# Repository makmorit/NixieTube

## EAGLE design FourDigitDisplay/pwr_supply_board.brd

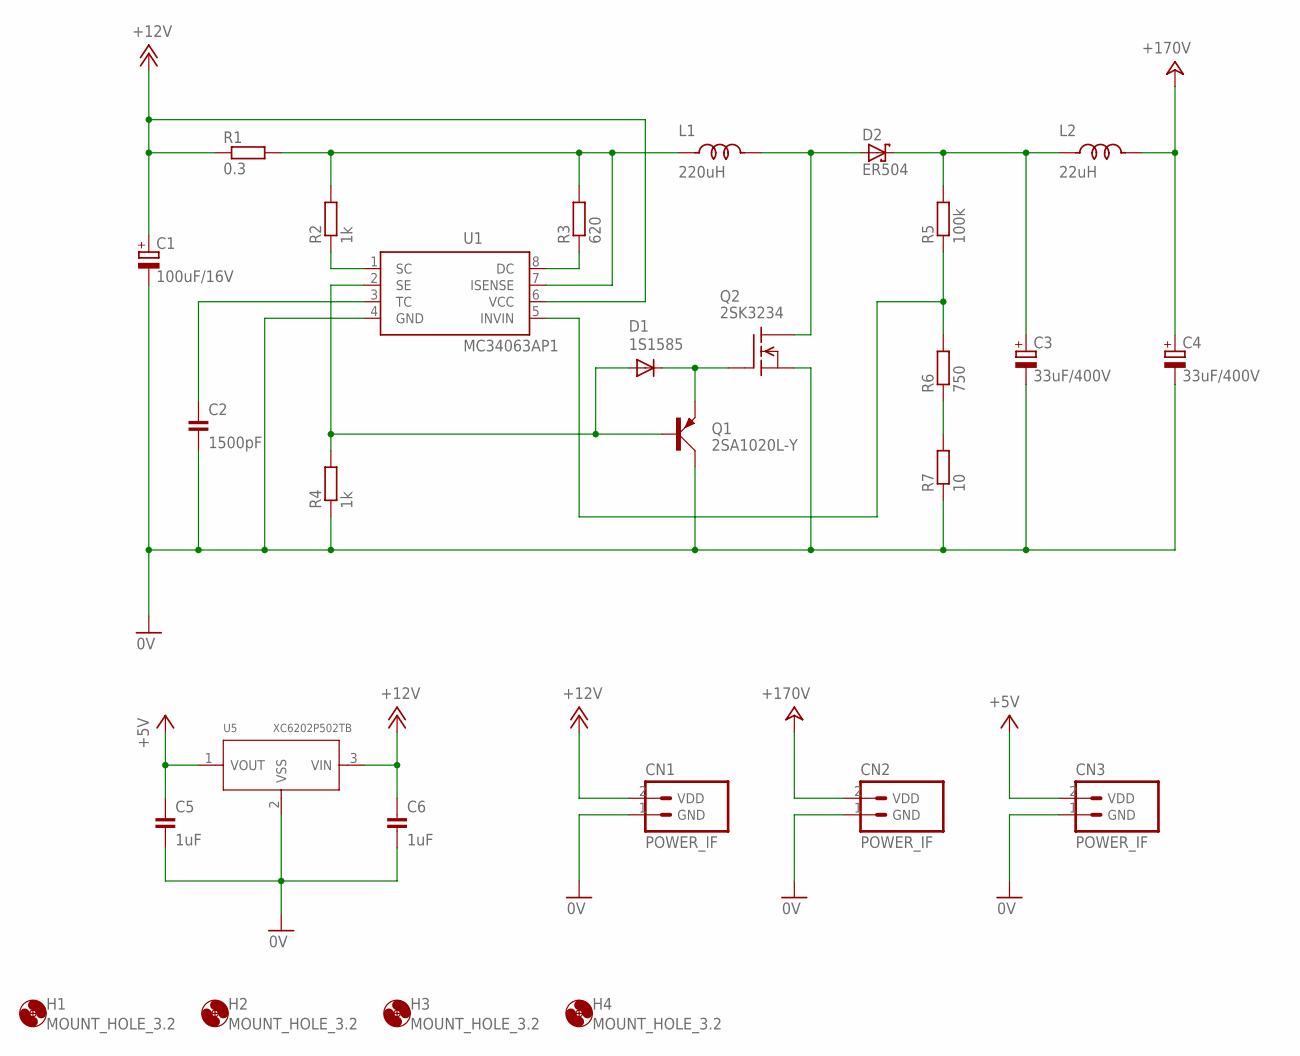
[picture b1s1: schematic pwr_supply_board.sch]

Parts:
C1: 100uF/16V; ELECAP_100MIL
C2: 1500pF; CAP_100MIL
C3, C4: 33uF/400V; ELECAP_300MIL
C5, C6: 1uF; CAP_100MIL
CN1, CN2, CN3: POWER_IF; HEADER_2PIN_POWER_IF
D1: 1S1585; DIODE-200MIL
D2: ER504; DIODE-500MIL
H1, H2, H3, H4: MOUNT_HOLE_3.2; 3,2
L1: 220uH; TOROID_COIL-300MIL
L2: 22uH; TOROID_COIL-300MIL
Q1: 2SA1020L-Y; TO-92NL
Q2: 2SK3234; TO-220
R1: 0.3; RESISTOR_0411_600MIL
R2, R4: 1k; RESISTOR_0411_600MIL
R3: 620; RESISTOR_0411_600MIL
R5: 100k; RESISTOR_0411_600MIL
R6: 750; RESISTOR_0411_600MIL
R7: 10; RESISTOR_0411_600MIL
U1: MC34063AP1; DIL08
U5: XC6202P502TB; TO92-LINE

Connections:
0V: C1.-, C2.2, C3.-, C4.-, C5.2, C6.2, CN1.1 (GND), CN2.1 (GND), CN3.1 (GND), Q1.2 (C), Q2.3 (S), R4.1, R7.1, U1.4 (GND), U5.2 (VSS)
+5V: C5.1, CN3.2 (VDD), U5.1 (VOUT)
+12V: C1.+, C6.1, CN1.2 (VDD), R1.1, U1.6 (VCC), U5.3 (VIN)
+24V: C4.+, CN2.2 (VDD), L2.2
unnamed: R3.1, U1.8 (DC)
unnamed: C3.+, D2.C, L2.1, R5.2
unnamed: C2.1, U1.3 (TC)
unnamed: R2.1, U1.1 (SC)
unnamed: L1.1, R1.2, R2.2, R3.2, U1.7 (ISENSE)
unnamed: R5.1, R6.2, U1.5 (INVIN)
unnamed: D1.A, Q1.3 (B), R4.2, U1.2 (SE)
unnamed: D1.C, Q1.1 (E), Q2.1 (G)
unnamed: R6.1, R7.2
unnamed: D2.A, L1.2, Q2.2 (D)

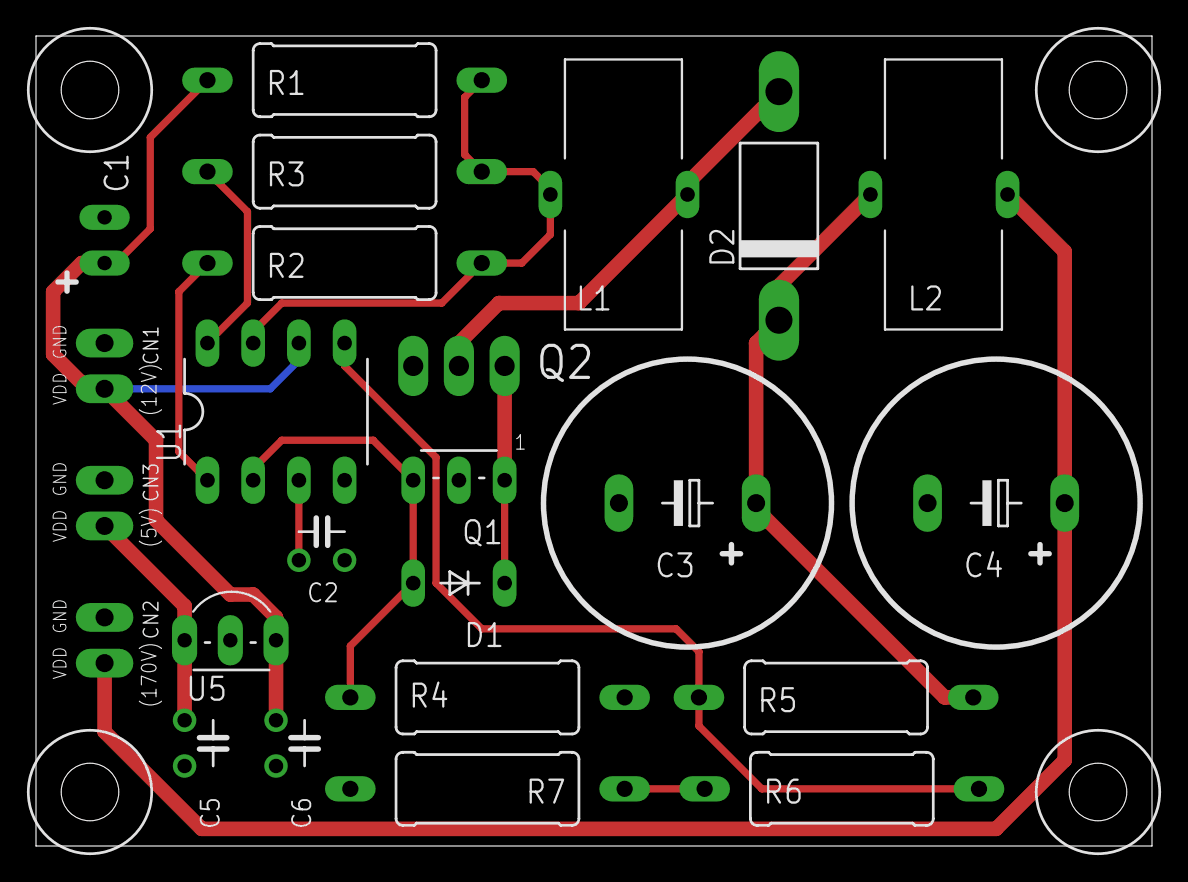
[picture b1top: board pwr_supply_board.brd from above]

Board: 2 copper layers, 62.0 x 45.0 mm, 28 parts (0 on the bottom side), 14 nets.

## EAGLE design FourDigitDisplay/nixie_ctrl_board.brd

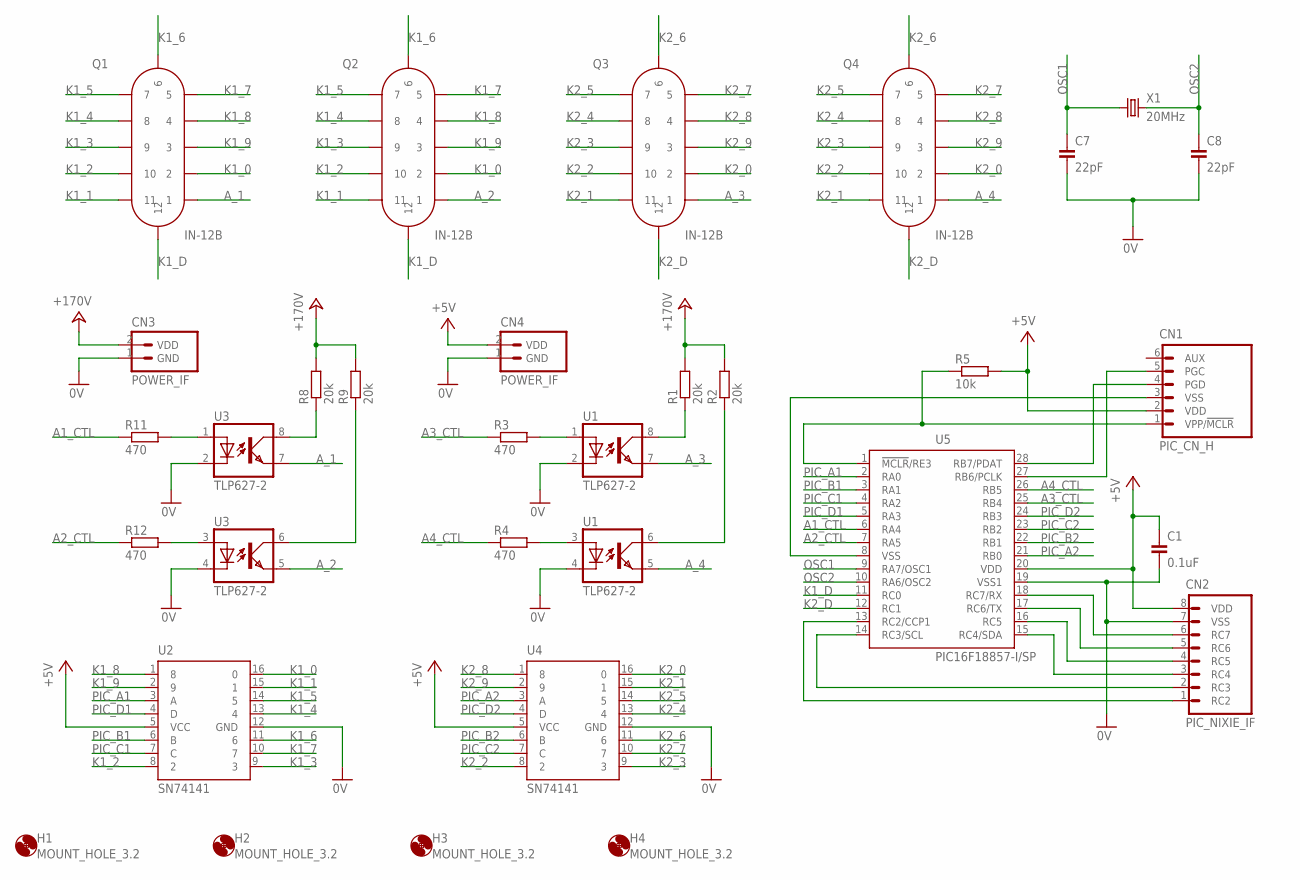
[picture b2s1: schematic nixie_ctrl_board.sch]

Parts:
C1: 0.1uF; CAP_100MIL
C7, C8: 22pF; CAP_100MIL
CN1: PIC_CN_H; HEADER_6PIN
CN2: PIC_NIXIE_IF; PIC_IF_NIXIE_8PIN
CN3, CN4: POWER_IF; HEADER_2PIN_POWER_IF
H1, H2, H3, H4: MOUNT_HOLE_3.2; 3,2
Q1, Q2, Q3, Q4: IN-12B; IN-12
R1, R2, R8, R9: 20k; RESISTOR_0207_300MIL
R3, R4, R11, R12: 470; RESISTOR_0204_200MIL
R5: 10k; RESISTOR_0204_200MIL
U1, U3: TLP627-2; DIL08
U2, U4: SN74141; DIL16
U5: PIC16F18857-I/SP; DIL28-3
X1: 20MHz; HC-49/S

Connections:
0V: C1.2, C7.2, C8.2, CN2.7 (VSS), CN3.1 (GND), CN4.1 (GND), U1.2 (C), U1.4 (C), U2.12 (GND), U3.2 (C), U3.4 (C), U4.12 (GND), U5.19 (VSS1)
+5V: C1.1, CN1.2 (VDD), CN2.8 (VDD), CN4.2 (VDD), R5.2, U2.5 (VCC), U4.5 (VCC), U5.20 (VDD)
+24V: CN3.2 (VDD), R1.2, R2.2, R8.2, R9.2
A1_CTL: R11.1, U5.6 (RA4)
A2_CTL: R12.1, U5.7 (RA5)
A3_CTL: R3.1, U5.25 (RB4)
A4_CTL: R4.1, U5.26 (RB5)
A_1: Q1.1, U3.7 (EMIT)
A_2: Q2.1, U3.5 (EMIT)
A_3: Q3.1, U1.7 (EMIT)
A_4: Q4.1, U1.5 (EMIT)
K1_0: Q1.2, Q2.2, U2.16 (0)
K1_1: Q1.11, Q2.11, U2.15 (1)
K1_2: Q1.10, Q2.10, U2.8 (2)
K1_3: Q1.9, Q2.9, U2.9 (3)
K1_4: Q1.8, Q2.8, U2.13 (4)
K1_5: Q1.7, Q2.7, U2.14 (5)
K1_6: Q1.6, Q2.6, U2.11 (6)
K1_7: Q1.5, Q2.5, U2.10 (7)
K1_8: Q1.4, Q2.4, U2.1 (8)
K1_9: Q1.3, Q2.3, U2.2 (9)
K1_D: Q1.12, Q2.12, U5.11 (RC0)
K2_0: Q3.2, Q4.2, U4.16 (0)
K2_1: Q3.11, Q4.11, U4.15 (1)
K2_2: Q3.10, Q4.10, U4.8 (2)
K2_3: Q3.9, Q4.9, U4.9 (3)
K2_4: Q3.8, Q4.8, U4.13 (4)
K2_5: Q3.7, Q4.7, U4.14 (5)
K2_6: Q3.6, Q4.6, U4.11 (6)
K2_7: Q3.5, Q4.5, U4.10 (7)
K2_8: Q3.4, Q4.4, U4.1 (8)
K2_9: Q3.3, Q4.3, U4.2 (9)
K2_D: Q3.12, Q4.12, U5.12 (RC1)
unnamed: R1.1, U1.8 (COL)
unnamed: R2.1, U1.6 (COL)
unnamed: R3.2, U1.1 (A)
unnamed: R4.2, U1.3 (A)
unnamed: CN2.6 (RC7), U5.18 (RC7/RX)
unnamed: CN2.5 (RC6), U5.17 (RC6/TX)
unnamed: CN1.1 (VPP/!MCLR), R5.1, U5.1 (!MCLR!/RE3)
unnamed: CN1.4 (PGD), U5.28 (RB7/PDAT)
unnamed: CN1.5 (PGC), U5.27 (RB6/PCLK)
unnamed: CN2.4 (RC5), U5.16 (RC5)
unnamed: R8.1, U3.8 (COL)
unnamed: R9.1, U3.6 (COL)
unnamed: R11.2, U3.1 (A)
unnamed: R12.2, U3.3 (A)
unnamed: CN1.3 (VSS), U5.8 (VSS)
unnamed: CN2.3 (RC4), U5.15 (RC4/SDA)
unnamed: CN2.2 (RC3), U5.14 (RC3/SCL)
unnamed: CN2.1 (RC2), U5.13 (RC2/CCP1)
OSC1: C7.1, U5.9 (RA7/OSC1), X1.1
OSC2: C8.1, U5.10 (RA6/OSC2), X1.2
PIC_A1: U2.3 (A), U5.2 (RA0)
PIC_A2: U4.3 (A), U5.21 (RB0)
PIC_B1: U2.6 (B), U5.3 (RA1)
PIC_B2: U4.6 (B), U5.22 (RB1)
PIC_C1: U2.7 (C), U5.4 (RA2)
PIC_C2: U4.7 (C), U5.23 (RB2)
PIC_D1: U2.4 (D), U5.5 (RA3)
PIC_D2: U4.4 (D), U5.24 (RB3)

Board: 2 copper layers, 30 parts (0 on the bottom side), 61 nets, no tracks yet.

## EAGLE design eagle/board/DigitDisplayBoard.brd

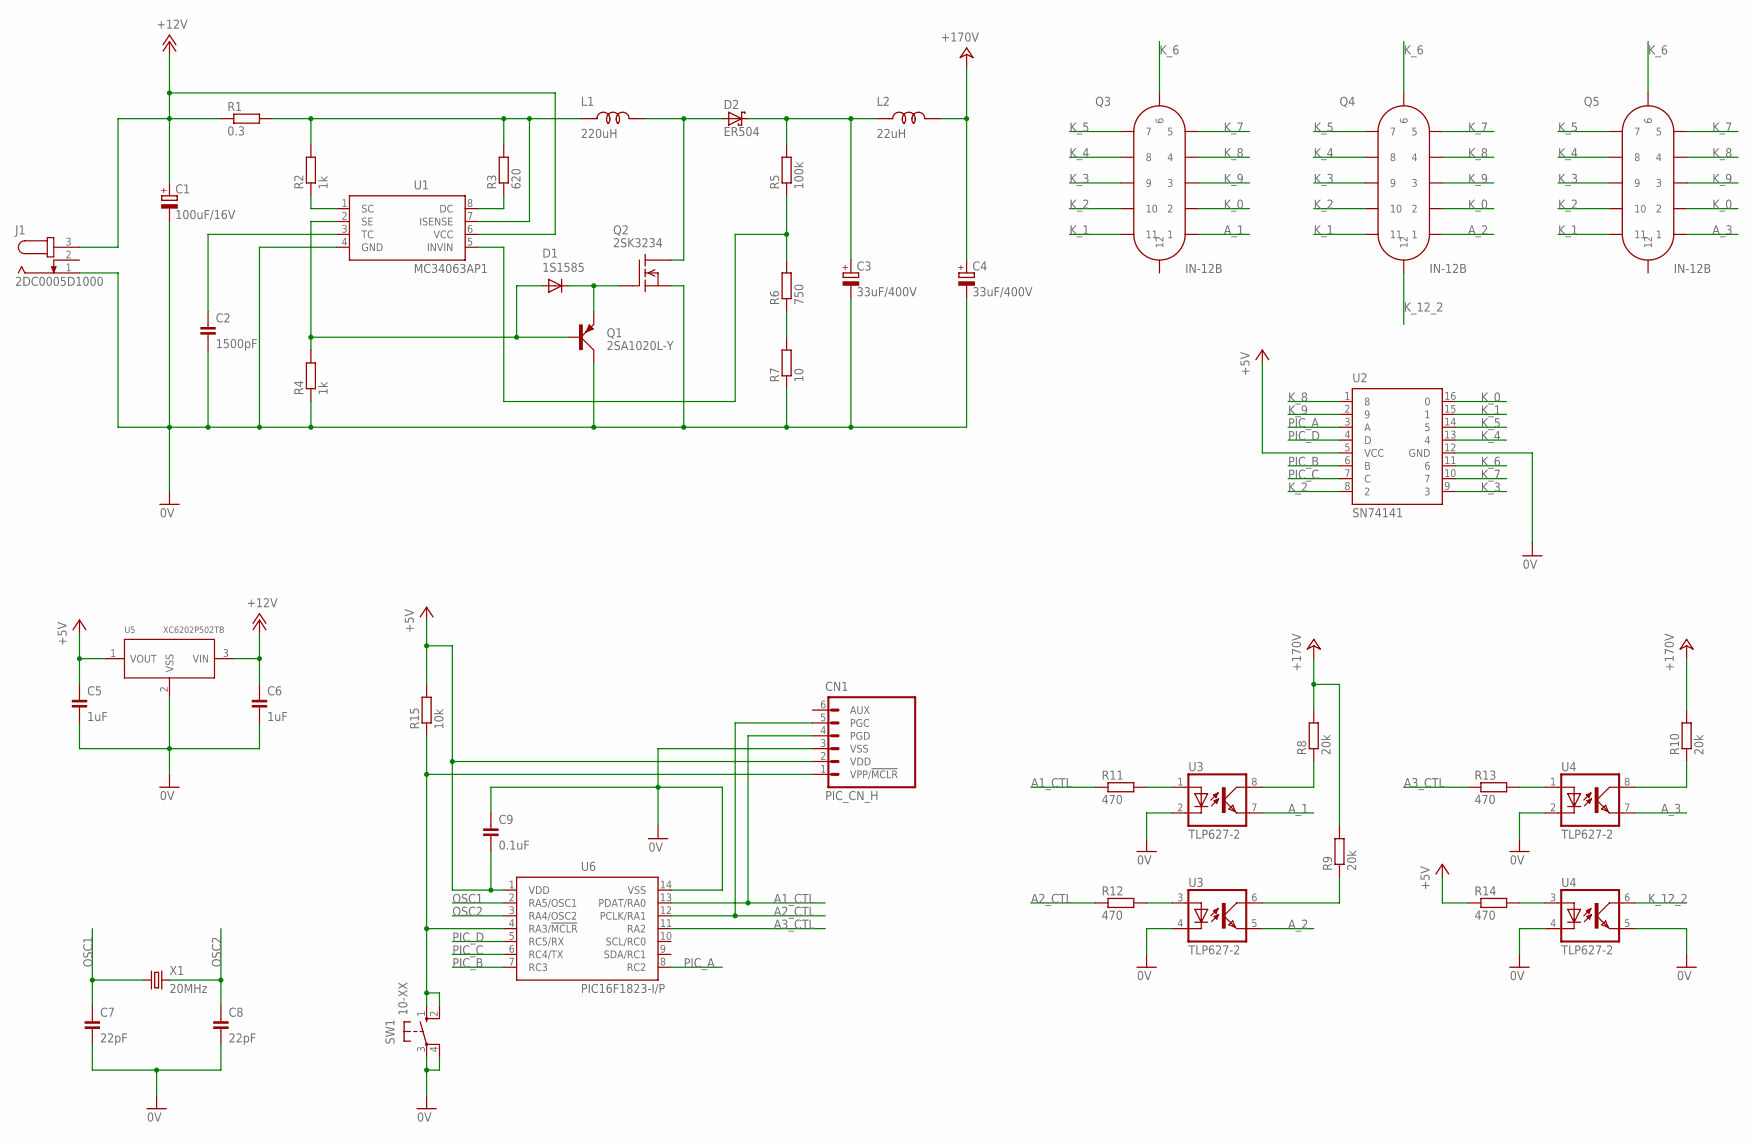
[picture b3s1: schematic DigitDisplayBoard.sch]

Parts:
C1: 100uF/16V; ELECAP_200MIL
C2: 1500pF; CAP_200MIL
C3, C4: 33uF/400V; ELECAP_300MIL
C5, C6: 1uF; CAP_200MIL
C7, C8: 22pF; CAP_200MIL
C9: 0.1uF; CAP_200MIL
CN1: PIC_CN_H; HEADER_6PIN
D1: 1S1585; DIODE-200MIL
D2: ER504; DIODE-500MIL
J1: 2DC0005D1000; DCJACK_2.1_5.5
L1: 220uH; TOROID_COIL-300MIL
L2: 22uH; TOROID_COIL-300MIL
Q1: 2SA1020L-Y; TO-92NL
Q2: 2SK3234; TO-220
Q3, Q4, Q5: IN-12B; IN-12
R1: 0.3; RESISTOR_0411_600MIL
R2, R4: 1k; RESISTOR_0411_600MIL
R3: 620; RESISTOR_0411_600MIL
R5: 100k; RESISTOR_0411_600MIL
R6: 750; RESISTOR_0411_600MIL
R7: 10; RESISTOR_0411_600MIL
R8, R10: 20k; RESISTOR_0207_300MIL
R9: 20k; RESISTOR_0411_600MIL
R11, R12, R13, R14: 470; RESISTOR_0207_300MIL
R15: 10k; RESISTOR_0207_300MIL
SW1: 10-XX; B3F-10XX
U1: MC34063AP1; DIL08
U2: SN74141; DIL16
U3, U4: TLP627-2; DIL08
U5: XC6202P502TB; TO92-LINE
U6: PIC16F1823-I/P; DIL14
X1: 20MHz; HC-49/S

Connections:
0V: C1.-, C2.2, C3.-, C4.-, C5.2, C6.2, C7.2, C8.2, C9.1, CN1.3 (VSS), J1.1, Q1.2 (C), Q2.3 (S), R4.1, R7.1, SW1.3, SW1.4 (P1), U1.4 (GND), U2.12 (GND), U3.2 (C), U3.4 (C), U4.2 (C), U4.4 (C), U4.5 (EMIT), U5.2 (VSS), U6.14 (VSS)
+5V: C5.1, C9.2, CN1.2 (VDD), R14.1, R15.2, U2.5 (VCC), U5.1 (VOUT), U6.1 (VDD)
+12V: C1.+, C6.1, J1.3, R1.1, U1.6 (VCC), U5.3 (VIN)
+24V: C4.+, L2.2, R8.2, R9.2, R10.2
A1_CTL: CN1.4 (PGD), R11.1, U6.13 (PDAT/RA0)
A2_CTL: CN1.5 (PGC), R12.1, U6.12 (PCLK/RA1)
A3_CTL: R13.1, U6.11 (RA2)
A_1: Q3.1, U3.7 (EMIT)
A_2: Q4.1, U3.5 (EMIT)
A_3: Q5.1, U4.7 (EMIT)
K_0: Q3.2, Q4.2, Q5.2, U2.16 (0)
K_1: Q3.11, Q4.11, Q5.11, U2.15 (1)
K_2: Q3.10, Q4.10, Q5.10, U2.8 (2)
K_3: Q3.9, Q4.9, Q5.9, U2.9 (3)
K_4: Q3.8, Q4.8, Q5.8, U2.13 (4)
K_5: Q3.7, Q4.7, Q5.7, U2.14 (5)
K_6: Q3.6, Q4.6, Q5.6, U2.11 (6)
K_7: Q3.5, Q4.5, Q5.5, U2.10 (7)
K_8: Q3.4, Q4.4, Q5.4, U2.1 (8)
K_9: Q3.3, Q4.3, Q5.3, U2.2 (9)
K_12_2: Q4.12, U4.6 (COL)
unnamed: R3.1, U1.8 (DC)
unnamed: C3.+, D2.C, L2.1, R5.2
unnamed: C2.1, U1.3 (TC)
unnamed: R2.1, U1.1 (SC)
unnamed: L1.1, R1.2, R2.2, R3.2, U1.7 (ISENSE)
unnamed: R5.1, R6.2, U1.5 (INVIN)
unnamed: D1.A, Q1.3 (B), R4.2, U1.2 (SE)
unnamed: D1.C, Q1.1 (E), Q2.1 (G)
unnamed: R6.1, R7.2
unnamed: D2.A, L1.2, Q2.2 (D)
unnamed: R8.1, U3.8 (COL)
unnamed: R9.1, U3.6 (COL)
unnamed: R11.2, U3.1 (A)
unnamed: R12.2, U3.3 (A)
unnamed: R14.2, U4.3 (A)
unnamed: R13.2, U4.1 (A)
unnamed: CN1.1 (VPP/!MCLR), R15.1, SW1.1 (S), SW1.2 (S1), U6.4 (RA3/!MCLR!)
unnamed: R10.1, U4.8 (COL)
OSC1: C7.1, U6.2 (RA5/OSC1), X1.1
OSC2: C8.1, U6.3 (RA4/OSC2), X1.2
PIC_A: U2.3 (A), U6.8 (RC2)
PIC_B: U2.6 (B), U6.7 (RC3)
PIC_C: U2.7 (C), U6.6 (RC4/TX)
PIC_D: U2.4 (D), U6.5 (RC5/RX)

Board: 2 copper layers, 43 parts (0 on the bottom side), 45 nets, no tracks yet.

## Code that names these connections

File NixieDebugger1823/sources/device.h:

#ifndef __DEVICE_H
#define __DEVICE_H

//
// タクトスイッチ
//
#define BUTTON_0 RA3

//
// 点灯制御用
//   SN74141制御用
//
#define PIC_A RC2
#define PIC_B RC3
#define PIC_C RC4
#define PIC_D RC5
//
//   TLP627制御用
//
#define TLP_A_1 RA0
#define TLP_A_2 RA1
#define TLP_A_3 RA2

// 関数
void port_init();

#endif // __DEVICE_H

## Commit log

2017-03-10 ライブラリーを大幅修正
2017-03-11 ライブラリーを小修正
2017-03-11 170V電源回路図の初版
2017-03-11 170V出力をターミナルブロックに変更
2017-03-11 データシートを格納
2017-03-15 実体配線図の初版
2017-03-15 ignoreリスト更新
2017-03-18 IC（２件）をライブラリーに追加
    SN74141
    PIC16F1823
2017-03-18 IC（１件）をライブラリーに追加
    TLP627
2017-03-20 部品（１件）をライブラリーに追加
    ニキシー管の初版（細かいところは後日修正予定）
2017-03-22 点灯制御の回路図初版
    足りない部品も追加
2017-03-23 点灯制御の回路図を修正
    PICのVDDが5Vにつながっていなかったので修正
2017-03-24 デバッグ用ファームウェアの初版
    Shift_JIS なのでコメントが化けてます
2017-03-25 デバッグ用ファームウェア修正
    以下の仮実装を追加
    ・ダイナミック点灯用の制御（２けた分）切替は10msごと
    ・タクトスイッチを押すと１００秒間カウントダウン
2017-04-01 ダイナミック点灯のロジックを修正
    ダイナミック点灯間隔（9msec）のうち、
    ・最初の3msecはアノードをOffとする
    ・次の6msecはアノードをOnとする
    よう修正しました。
2017-04-02 ３桁表示（M.SS形式）対応
    ・コメントをShift_JISからUTF-8へ変更
    ・カウンター残秒数を３桁（M.SS形式）で表示できるよう修正
    ・３分間（１８０秒間）のカウンターに変更（表示が3.00-->2.59-->...-->0.01-->0.00）と変わるようになります
2017-04-02 ダイナミック点灯のロジックを修正
    ダイナミック点灯間隔（9msec）のうち、
    ・最初の0.8msecはアノードをOffとする
    ・次の3.2msecはアノードをOnとする
    よう修正しました。
    この対応によりニキシー点灯時の「ちらつき」が若干解消しました。
    ついでに、不要となった処理／変数を削除しています。
2017-04-04 ３桁表示用基板の回路図の初版
    部品を１点追加しています
2017-04-04 ３桁表示用基板の使用部品を修正
    ライブラリーを修正（抵抗器）
    基板で使用する部品の見直し
2017-04-23 回路図を修正
    ・I2Cインターフェースを新設
    ・小数点(DOT)の表示位置変更（または非表示）を可能とする
2017-04-23 PICファームウェアをMPLAB X IDE用に再編成
2017-04-23 不要リソースを削除
2017-04-23 コメントを修正
2017-04-23 ignore追加
2017-04-30 ignore更新
2017-04-30 不要ファイルの削除
2017-08-07 ４桁表示器の初版
    回路図はまだ空です。
2017-08-08 電源回路図の初版
    12Vから170V、5Vの２電源を生成し出力させる回路
2017-08-08 マウントホール追加
2017-08-08 部品配置
2017-08-09 制御基板の初版
    まだニキシー管を配置しただけ
2017-08-10 IC群を追加して仮置き
2017-08-11 配線の追加
2017-08-13 部品配置修正
2017-08-15 電源基板の部品配線
2017-08-17 配線を一部修正
2017-09-15 制御ボードの開発を中止
2017-09-15 電源回路の部品配置を確定
